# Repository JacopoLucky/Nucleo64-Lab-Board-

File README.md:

# Nucleo64-Lab-Board
Here there are all the file for the Nucleo64 (STM32F334R8) laboratory board for the Industrial electronic course at UNIPD

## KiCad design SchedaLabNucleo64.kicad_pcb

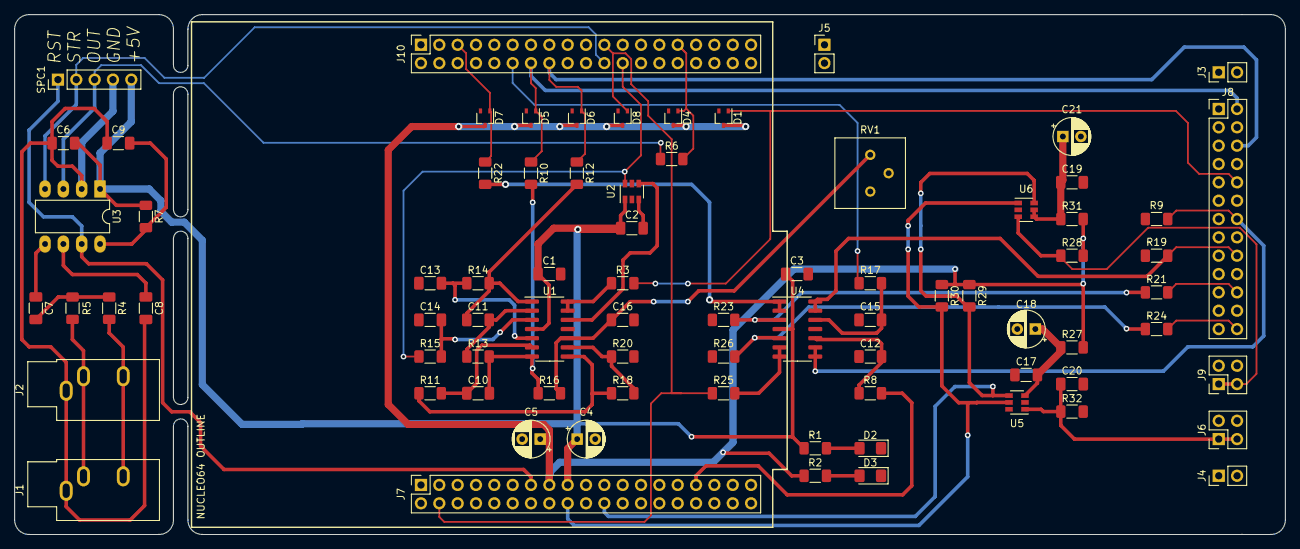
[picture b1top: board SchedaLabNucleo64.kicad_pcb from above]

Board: 2 copper layers, 176.0 x 72.0 mm, 79 parts (0 on the bottom side), 50 nets.

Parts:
C1, C2, C3, C6, C8, C17, C19: 100nF; C_1206_3216Metric_Pad1.33x1.80mm_HandSolder
C4, C5, C18, C21: 10uF; CP_Radial_D5.0mm_P2.50mm
C7, C12, C15: 1nF; C_1206_3216Metric_Pad1.33x1.80mm_HandSolder
C9: 33pF; C_1206_3216Metric_Pad1.33x1.80mm_HandSolder
C10, C11, C13, C14, C16: 10nF; C_1206_3216Metric_Pad1.33x1.80mm_HandSolder
C20: 200pF; C_1206_3216Metric_Pad1.33x1.80mm_HandSolder
D1, D4, D5, D6, D7, D8: BAT54W; SOT-323_SC-70
D2, D3: LED; LED_1206_3216Metric_Pad1.42x1.75mm_HandSolder
J1, J2: AudioJack3; Jack_3.5mm_CUI_SJ1-3533NG_Horizontal
J3, J4, J5: Conn_01x02_Male; PinHeader_1x02_P2.54mm_Vertical
J6, J9: Conn_02x02_Odd_Even; PinHeader_2x02_P2.54mm_Vertical
J7, J10: Conn_02x19_Odd_Even; PinSocket_2x19_P2.54mm_Vertical
J8: Conn_02x13_Odd_Even; PinHeader_2x13_P2.54mm_Vertical
R1: 100; R_1206_3216Metric_Pad1.30x1.75mm_HandSolder
R2: 60R4; R_1206_3216Metric_Pad1.30x1.75mm_HandSolder
R3, R6, R10, R12, R22, R25: 200; R_1206_3216Metric_Pad1.30x1.75mm_HandSolder
R4, R5: 22k; R_1206_3216Metric_Pad1.30x1.75mm_HandSolder
R7: 200k; R_1206_3216Metric_Pad1.30x1.75mm_HandSolder
R8, R13, R15, R17, R20: 1k; R_1206_3216Metric_Pad1.30x1.75mm_HandSolder
R9, R11, R14, R16, R19: 10k; R_1206_3216Metric_Pad1.30x1.75mm_HandSolder
R18: 29k; R_1206_3216Metric_Pad1.30x1.75mm_HandSolder
R21, R24: 20k; R_1206_3216Metric_Pad1.30x1.75mm_HandSolder
R23, R26: 30k; R_1206_3216Metric_Pad1.30x1.75mm_HandSolder
R27, R31: 10; R_1206_3216Metric_Pad1.30x1.75mm_HandSolder
R28, R29, R30: 4k7; R_1206_3216Metric_Pad1.30x1.75mm_HandSolder
R32: 2k; R_1206_3216Metric_Pad1.30x1.75mm_HandSolder
RV1: 1k; Potentiometer_Bourns_3386P_Vertical
SPC1: Conn_01x05_Male; PinHeader_1x05_P2.54mm_Vertical
U1, U4: LM6134; SOIC-14_3.9x8.7mm_P1.27mm
U2: TS5A3159ADBVR; SOT-23-6
U3: MSGEQ7; DIP-8_W7.62mm_LongPads
U5: DAC7571; SOT-23-6
U6: TMP101; SOT-23-6

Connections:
+3V3: C5.1, D1.3, D4.3, D5.3, D6.3, D7.3, D8.3, J7.15, R2.1, R27.2, R28.2, R29.1, R30.1, R31.2
+5V: C1.1, C2.1, C3.1, C4.1, C6.2, J7.17, R1.1, R7.1, SPC1.5, U1.4, U2.1, U3.1, U4.4
ADC2(3): D5.1, J8.2, J10.14, R10.1
ADC2(4): D6.1, J8.6, J10.16, R12.1
ADC2(5): D4.1, J10.29, R6.2
ADC2(11): D7.1, J10.5, R22.1
ADC2(12): D8.1, J7.4, J10.21, R25.1
ALERT: J9.1, J9.3, R28.1, U6.3
DAC1(1): J7.31, R8.2
DAC1(2): J10.12, R17.2
ExtDAC_OUT: C20.1, J6.1, J6.3, R32.1, U5.1
ExtIn1: J8.22, R21.2
ExtIn2: J8.26, R24.2
GND: C1.2, C2.2, C3.2, C4.2, C5.2, C6.1, C8.2, C9.2, C12.2, C13.2, C14.2, C15.2, C16.2, C17.1, C18.2, C19.2, C20.2, C21.2, D2.1, D3.1, J1.S, J2.S, J3.1, J3.2, J4.1, J4.2, J5.1, J5.2, J6.2, J6.4, J7.7, J7.19, J7.20, J7.21, J8.1, J8.3, J8.4, J8.5, J8.7, J8.8, J8.9, J8.11, J8.12, J8.13, J8.15, J8.16, J8.17, J8.19, J8.20, J8.21, J8.23, J8.24, J8.25, J9.2, J9.4, J10.10, R9.2, R19.2, R20.2, R23.2, R26.2, R32.2, RV1.1, RV1.2, SPC1.4, U1.11, U2.3, U3.2, U4.11, U5.2, U5.6, U6.2
unnamed: C7.1, U3.5
unnamed: C7.2, R4.1, R5.2
unnamed: C8.1, U3.6
unnamed: C9.1, R7.2, U3.8
unnamed: C10.2, R11.1, U1.6
unnamed: C11.1, R12.2, R14.2, U1.1
unnamed: C11.2, R13.1, U1.2
unnamed: C12.1, R8.1, U4.10
unnamed: C13.1, R14.1, U1.5
unnamed: C14.1, R15.1, U1.3
unnamed: C15.1, R17.1, U4.12
unnamed: C16.1, R16.2, RV1.3, U1.10
unnamed: C17.2, C18.1, R27.1, U5.3
unnamed: C19.1, C21.1, R31.1, U6.4, U6.5
unnamed: D2.2, R1.2
unnamed: D3.2, R2.2
unnamed: J1.R, J2.R, R4.2
unnamed: J1.T, J2.T, R5.1
unnamed: R3.1, U1.13, U1.14
unnamed: R18.2, R20.1, U1.9
unnamed: R21.1, R23.1, U4.3
unnamed: R22.2, U4.1, U4.2
unnamed: R24.1, R26.1, U4.5
unnamed: R25.2, U4.6, U4.7
unnamed: U1.12, U2.4
ODAC1(1): J8.14, R9.1, U4.8, U4.9
ODAC1(2): J8.18, R19.1, U4.13, U4.14
OSPC: R6.1, SPC1.3, U3.3
PWM: D1.1, J8.10, R3.2
RST: J7.13, SPC1.1, U3.7
SCL: J7.18, R30.2, U5.5, U6.1
SDA: J7.22, R29.2, U5.4, U6.6
STROBE: J10.22, SPC1.2, U3.4
VPWM: J10.24, R15.2, U2.6
X2: C10.1, R10.2, R13.2, R16.1, U1.7
aX2: R11.2, R18.1, U1.8
